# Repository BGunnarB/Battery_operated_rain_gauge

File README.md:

# Battery_operated_rain_gauge

This project is for a battery-operated (2 x AA) rain-gauge using the MySensors library.

The requirements were that the gauge should report the rainfall during the last 5 to 10 minutes to the controller. Since the node should be asleep most of the time it would not be able to keep track of the time between reports, so some other way of time-keeping should be provided.

Also, the tipping-bucket rain-gauge typically generated contact bounce, which has to be filtered out.

The solution is based on an Arduino Pro-Mini 8 MHz, 3.3 V and the NRF24L01+ radio. Timing is provided by a CMOS 555 timer which generates one pulse every minute. Every minute-pulse generates an interrupt. After a pre-set number of minute pulses, the rainfall and battery status are reported. 

Every time the bucket tips, an interrupt is generated. The rainfall is incremented by the amount that the bucket indicates. The calibration factor is set in the sketch. The contact bounce is filtered out by another CMOS 555 timer since I had a few of these handy rather than messing around with software filtering, which may disrupt the interrupt service routine.

To indicate that the timer generated an interrupt, a LED flashes green. To indicate that the rain-bucket generated an interrupt, the LED flashes red.

The battery sensor circuit is off the pcb but is the usual voltage divider 1M in series with 470k found elsewhere on the MySensors webpage. A capacitor of 100 nF is added across the 470k resistor for decoupling of noise.

It is up to the controller (in my case OpenHAB) to sum up the rainfall during e.g. 24 hours. The rain-gauge simply reports the rainfall during the elapsed period.

The total power consumption by the circuit is 240 nA when sleeping. The LED on the Arduino has been removed but not the power regulator.

The PCB was designed in KiCad and the board produced by OSHPark in the US.

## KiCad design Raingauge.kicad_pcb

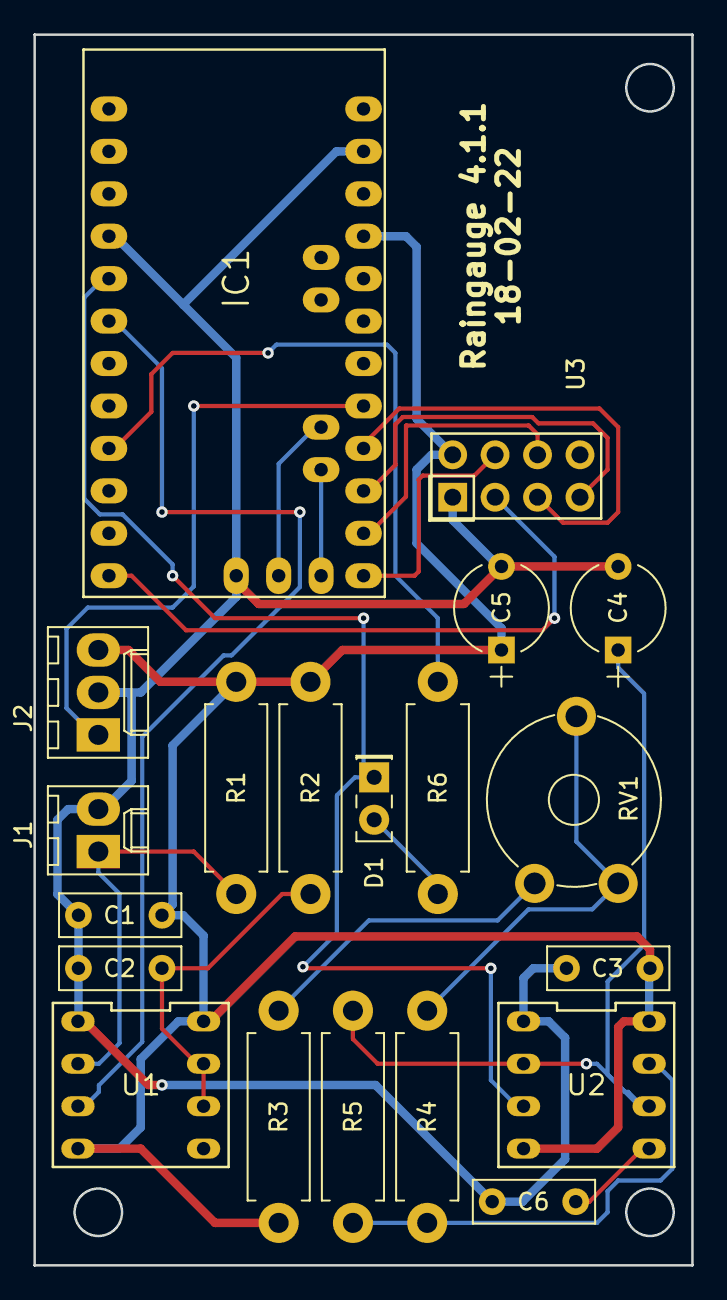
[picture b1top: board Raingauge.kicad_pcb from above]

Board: 2 copper layers, 39.4 x 73.7 mm, 20 parts (0 on the bottom side), 19 nets.

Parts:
C1, C2, C3: 100n; C_Rect_L7.2mm_W2.5mm_P5.00mm_FKS2_FKP2_MKS2_MKP2
C4, C5: 22u; CP_Radial_Tantal_D5.5mm_P5.00mm
C6: 10n; C_Rect_L7.2mm_W2.5mm_P5.00mm_FKS2_FKP2_MKS2_MKP2
D1: LED_Dual_2pin; LED_Rectangular_W5.0mm_H2.0mm
IC1: ArduinoProMini; pro_mini
J1: Bucket; Molex_KK-6410-02_02x2.54mm_Straight
J2: Battery; Molex_KK-6410-03_03x2.54mm_Straight
R1: 33k; R_Axial_DIN0411_L9.9mm_D3.6mm_P12.70mm_Horizontal
R2, R4: 1M; R_Axial_DIN0411_L9.9mm_D3.6mm_P12.70mm_Horizontal
R3: 2.5M; R_Axial_DIN0411_L9.9mm_D3.6mm_P12.70mm_Horizontal
R5: 22k; R_Axial_DIN0411_L9.9mm_D3.6mm_P12.70mm_Horizontal
R6: 56; R_Axial_DIN0411_L9.9mm_D3.6mm_P12.70mm_Horizontal
RV1: 1M; Potentiometer_Trimmer_Piher_PT-10v10_Horizontal_Px10.0mm_Py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
U1, U2: LMC555xN; DIP-8_0_ELL
U3: NRF24L01

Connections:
/BAT_SENSE: IC1.17, J2.1
GND: C1.2, C2.2, C3.2, C4.2, C5.2, C6.2, IC1.4, IC1.23, IC1.29, J1.2, J2.2, U1.1, U2.1, U3.1
unnamed: C2.1, R2.2, U1.6, U1.7
unnamed: C4.1, R5.2, U2.2, U2.6
unnamed: C6.1, U2.5
unnamed: D1.1, IC1.5, U2.3
unnamed: D1.2, R6.2
unnamed: IC1.6, U1.3
unnamed: IC1.9, R6.1
unnamed: IC1.12, U3.3
unnamed: IC1.13, U3.4
unnamed: IC1.14, U3.6
unnamed: IC1.15, U3.7
unnamed: IC1.16, U3.5
unnamed: J1.1, R1.2, U1.2
unnamed: R3.2, RV1.3
unnamed: R4.1, RV1.1, RV1.2
unnamed: R4.2, R5.1, U2.7
VCC: C1.1, C3.1, C5.1, IC1.21, J2.3, R1.1, R2.1, R3.1, U1.4, U1.8, U2.4, U2.8, U3.2

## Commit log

2018-05-01 First project description
    First commit
2018-05-01 Edits and more files
    Edited README.MD and added the Arduino sketch.
2018-05-01 Added image of pcb
2018-05-01 Edit Readme.md
2018-05-01 Added BOM
2018-05-02 Added pictures and edited readme
2018-05-03 Added Gerber files
